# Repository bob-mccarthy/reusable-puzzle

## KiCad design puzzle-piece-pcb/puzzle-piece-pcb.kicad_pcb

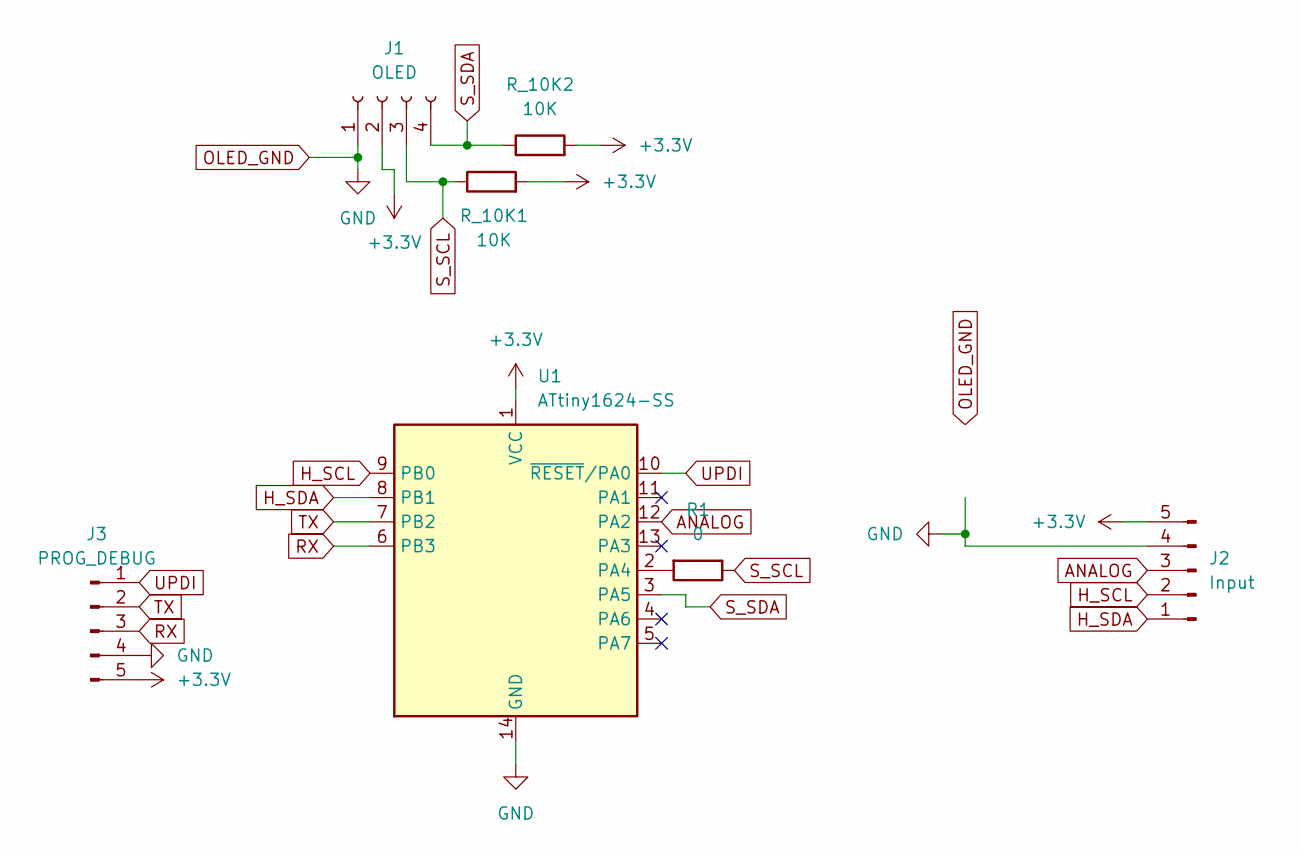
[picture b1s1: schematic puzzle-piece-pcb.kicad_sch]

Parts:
J1: OLED; PinSocket_1x04_P2.54mm_Vertical
J2: Input; PinSocket_1x05_P2.54mm_Vertical_SMD_Pin1Left
J3: PROG_DEBUG; PinSocket_1x05_P2.54mm_Vertical_SMD_Pin1Left
R1: 0; R_1206_3216Metric
R_10K1, R_10K2: 10K; R_1206_3216Metric
U1: ATtiny1624-SS; SOIC-14_3.9x8.7mm_P1.27mm

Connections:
+3.3V: J1.2, J2.5, J3.5, R_10K1.2, R_10K2.2, U1.1 (VCC)
ANALOG: J2.3, U1.12 (PA2)
H_SCL: J2.2, U1.9 (PB0)
H_SDA: J2.1, U1.8 (PB1)
unnamed: R1.2, U1.2 (PA4)
OLED_GND: J1.1, J2.4, J3.4, U1.14 (GND)
RX: J3.3, U1.6 (PB3)
S_SCL: J1.3, R1.1, R_10K1.1
S_SDA: J1.4, R_10K2.1, U1.3 (PA5)
TX: J3.2, U1.7 (PB2)
UPDI: J3.1, U1.10 (~RESET/PA0)

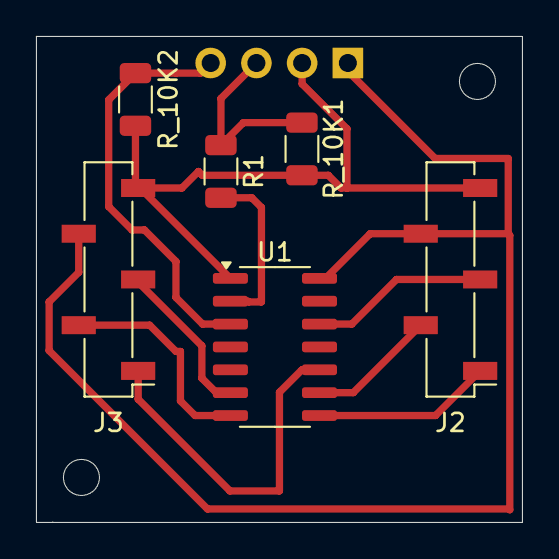
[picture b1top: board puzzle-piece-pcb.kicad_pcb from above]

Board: 2 copper layers, 27.0 x 27.0 mm, 7 parts (1 on the bottom side), 11 nets.

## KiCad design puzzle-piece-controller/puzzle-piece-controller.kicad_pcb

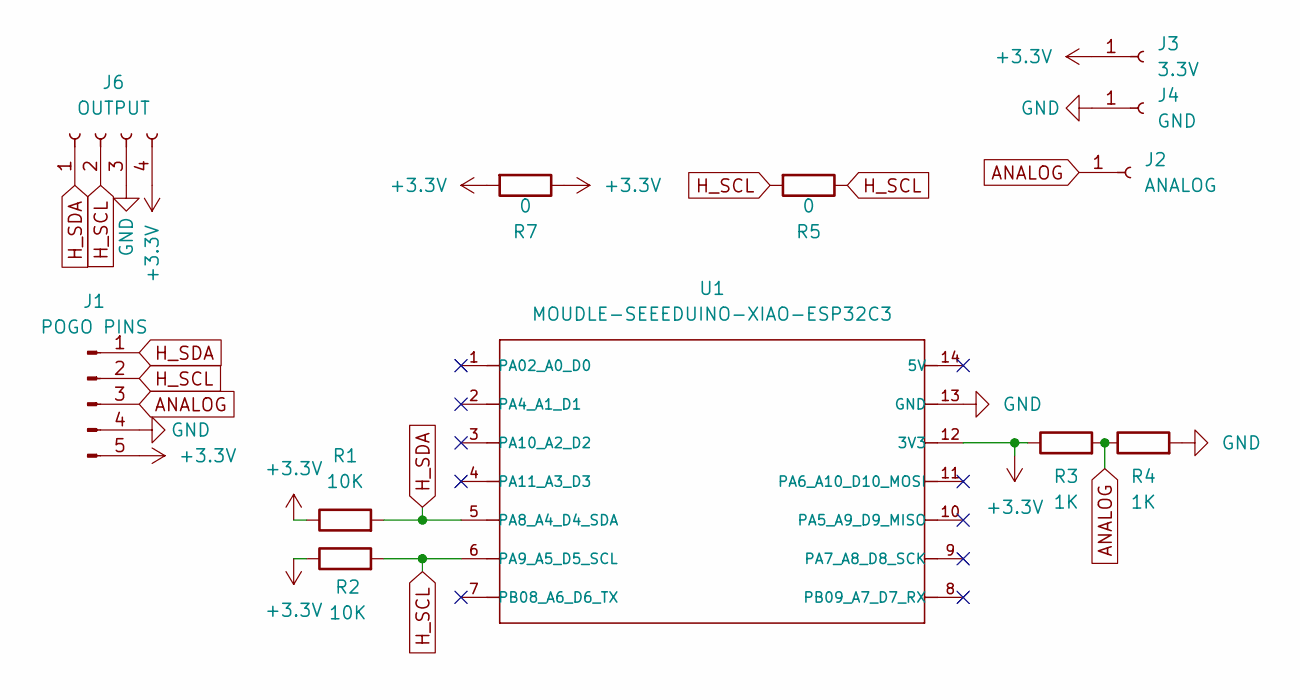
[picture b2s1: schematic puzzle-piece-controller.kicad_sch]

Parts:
J1: POGO PINS; PinHeader_1x05_P2.54mm_Vertical
J2: ANALOG; PinSocket_1x01_P2.54mm_Vertical
J3: 3.3V; PinSocket_1x01_P2.54mm_Vertical
J4: GND; PinSocket_1x01_P2.54mm_Vertical
J6: OUTPUT; PinSocket_1x04_P2.54mm_Vertical
R1, R2: 10K; R_1206_3216Metric_Pad1.30x1.75mm_HandSolder
R3, R4: 1K; R_1206_3216Metric_Pad1.30x1.75mm_HandSolder
R5, R7: 0; R_1206_3216Metric_Pad1.30x1.75mm_HandSolder
U1: MOUDLE-SEEEDUINO-XIAO-ESP32C3; SeeedStudio_XIAO_ESP32C3

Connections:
+3.3V: J1.5, J3.1, J6.4, R1.1, R2.1, R3.1, R7.1, R7.2, U1.12 (3V3)
ANALOG: J1.3, J2.1, R3.2, R4.1
GND: J1.4, J4.1, J6.3, R4.2, U1.13 (GND)
H_SCL: J1.2, J6.2, R2.2, R5.1, R5.2, U1.6 (PA9_A5_D5_SCL)
H_SDA: J1.1, J6.1, R1.2, U1.5 (PA8_A4_D4_SDA)

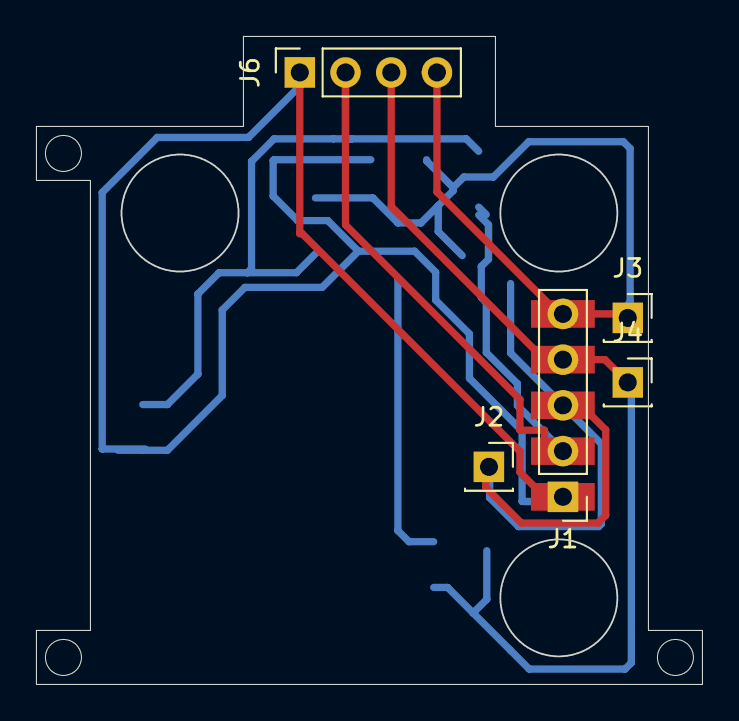
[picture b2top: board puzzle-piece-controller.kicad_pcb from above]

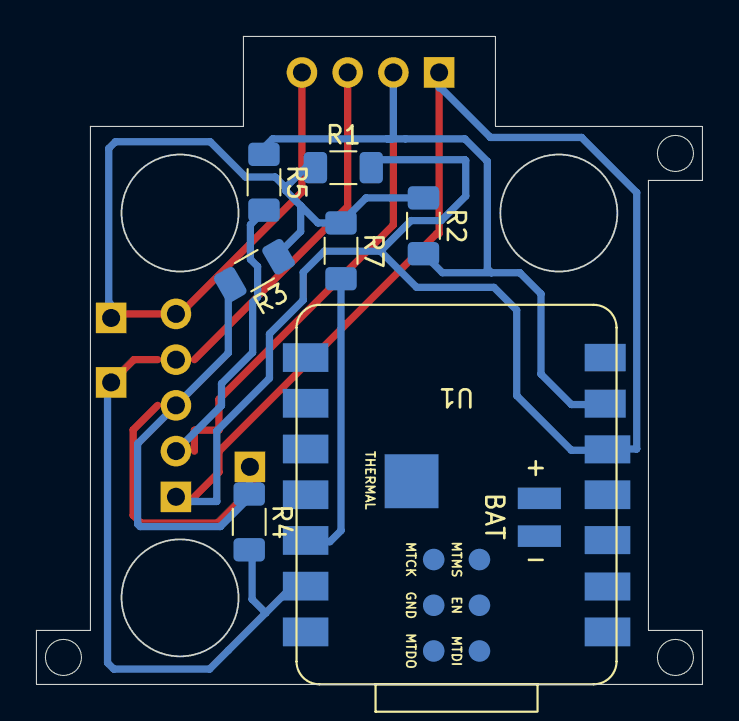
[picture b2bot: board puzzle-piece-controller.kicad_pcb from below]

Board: 2 copper layers, 36.9 x 36.0 mm, 12 parts (7 on the bottom side), 5 nets.

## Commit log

2024-08-22 initialized repo
2024-08-26 made drawing interface
2024-10-12 initializing reusable puzzle
2024-10-12 made puzzle piece pcb one sided
2024-10-14 made battery controller singled sided and removed lipo
2024-10-14 fixed transistor in battery pcb
2024-10-14 added puzzle-piece-battery-pcb.kicad_prl do not know why it was not originally included in last commit
2024-10-14 made controller pcb single sided
2024-10-16 add unrouted output throughholes to controller, and mounting holes
2024-10-17 updated gitignore
2024-11-01 made puzzle-controller board double sided
2024-11-12 current puzzle with attiny and pogo pins
2024-11-30 interface working with one picture for all puzzle pieces
2024-12-01 spacing mask working properly
